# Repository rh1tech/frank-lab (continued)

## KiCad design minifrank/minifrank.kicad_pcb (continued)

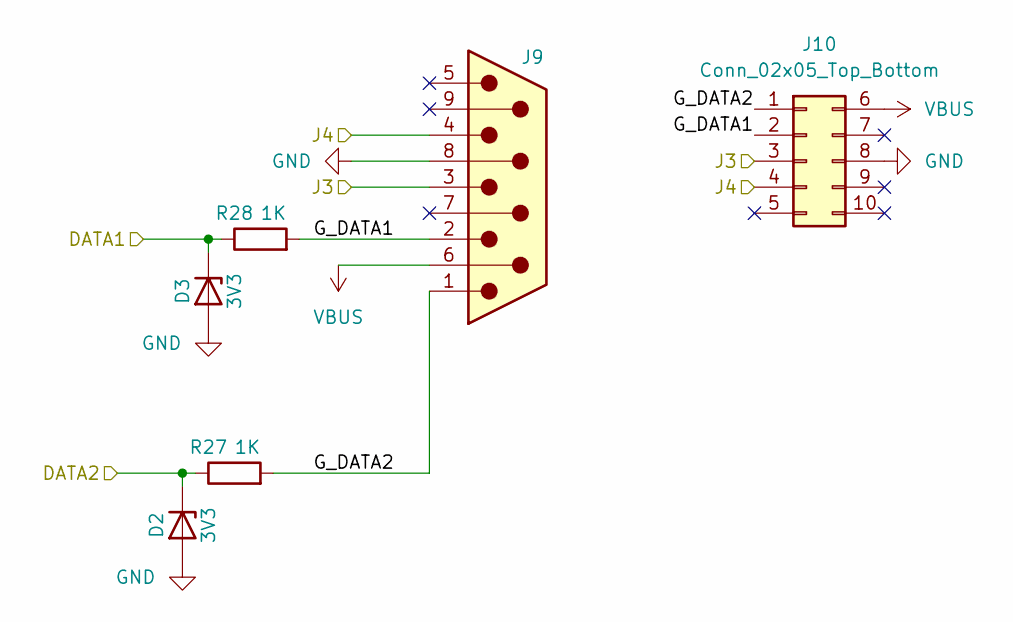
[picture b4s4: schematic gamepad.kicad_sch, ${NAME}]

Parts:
D2, D3: 3V3; Diode (SOD-323)
J9: GP2; DSUB-9_Male_TopMount
J10: Conn_02x05_Top_Bottom; IDC-Header_2x05_P2.54mm_Vertical
R27, R28: 1K; R_0603_1608Metric

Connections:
/GPIO20: J9.4, J10.4; also elsewhere on the board
/GPIO21: J9.3, J10.3; also elsewhere on the board
/GPIO26: D3.1 (K), R28.1; also elsewhere on the board
/GPIO27: D2.1 (K), R27.1; also elsewhere on the board
/Gamepad/G_DATA1: J9.2, J10.2, R28.2
/Gamepad/G_DATA2: J9.1, J10.1, R27.2

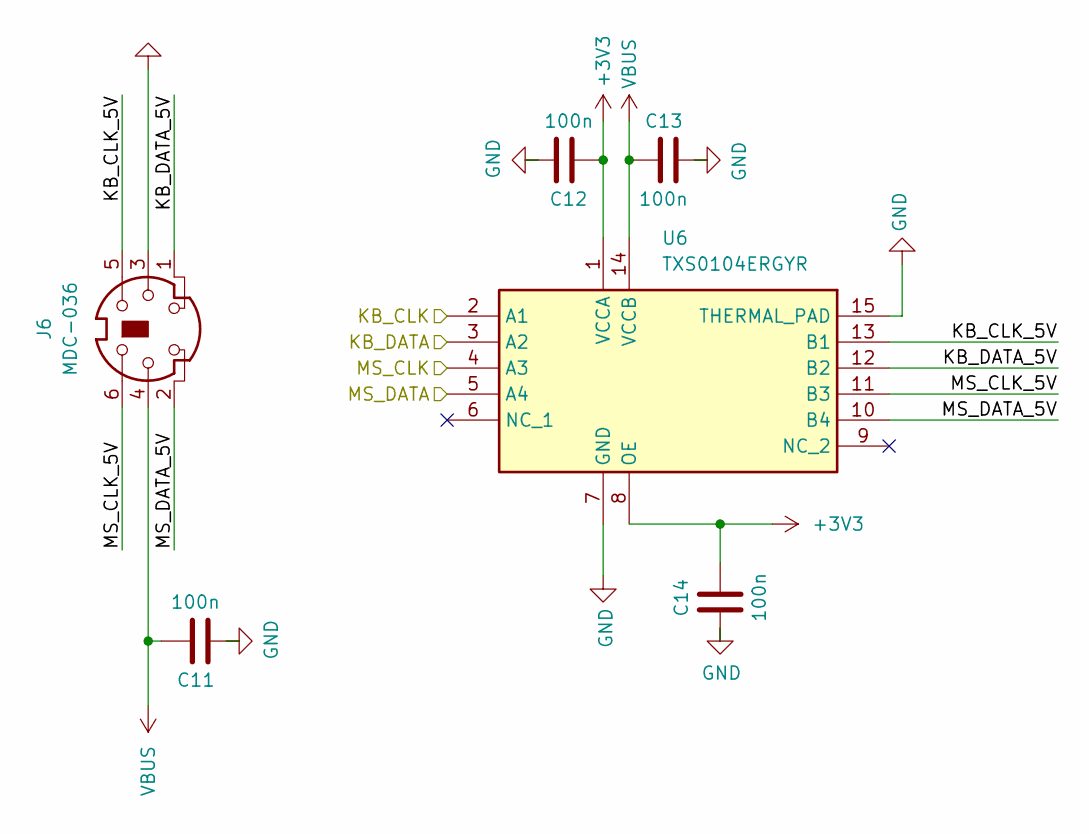
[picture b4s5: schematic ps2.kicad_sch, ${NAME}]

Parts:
C11, C12, C13, C14: 100n; C_0603_1608Metric
J6: MDC-036; MiniDIN (6 Pin, female)
U6: TXS0104ERGYR; RGY_S-PVQFN-N14_; Mouser Part Number 595-TXS0104ERGYR

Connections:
+3V3: C12.1, C14.1, U6.1 (VCCA), U6.8 (OE); also elsewhere on the board
/GPIO0: U6.4 (A3); also elsewhere on the board
/GPIO1: U6.5 (A4); also elsewhere on the board
/GPIO2: U6.2 (A1); also elsewhere on the board
/GPIO3: U6.3 (A2); also elsewhere on the board
/PS2/KB_CLK_5V: J6.5, U6.13 (B1)
/PS2/KB_DATA_5V: J6.1, U6.12 (B2)
/PS2/MS_CLK_5V: J6.6, U6.11 (B3)
/PS2/MS_DATA_5V: J6.2, U6.10 (B4)

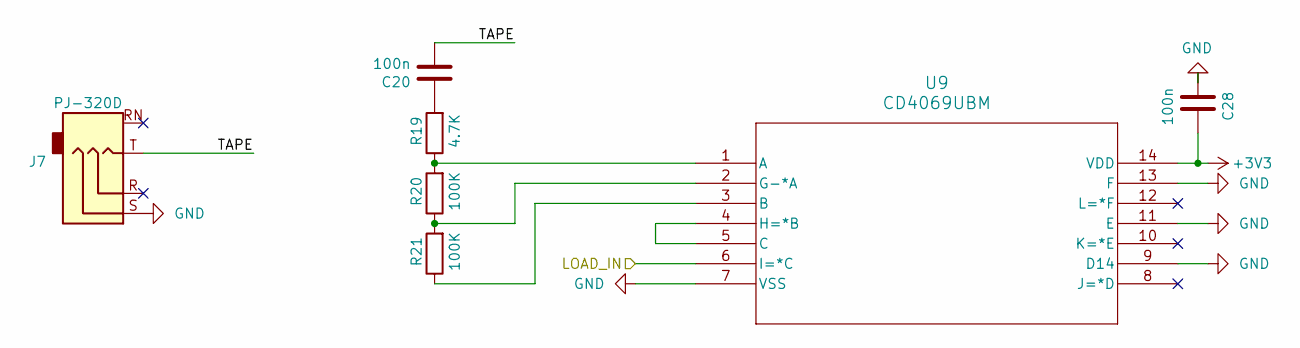
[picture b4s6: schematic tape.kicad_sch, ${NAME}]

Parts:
C20, C28: 100n; C_0603_1608Metric
J7: PJ-320D; Jack (3.5mm, PJ-320D, TapeIn)
R19: 4.7K; R_0603_1608Metric
R20, R21: 100K; R_0603_1608Metric
U9: CD4069UBM; SOIC127P600X175-14N

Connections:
+3V3: C28.1, U9.14 (VDD); also elsewhere on the board
/Tape In/LOAD_IN: U9.6 (I=*C); also elsewhere on the board
/Tape In/TAPE: C20.2, J7.T
unnamed: C20.1, R19.2
unnamed: R19.1, R20.2, U9.1 (A)
unnamed: R21.1, U9.3 (B)
unnamed: U9.4 (H=*B), U9.5 (C)
unnamed: R20.1, R21.2, U9.2 (G-*A)

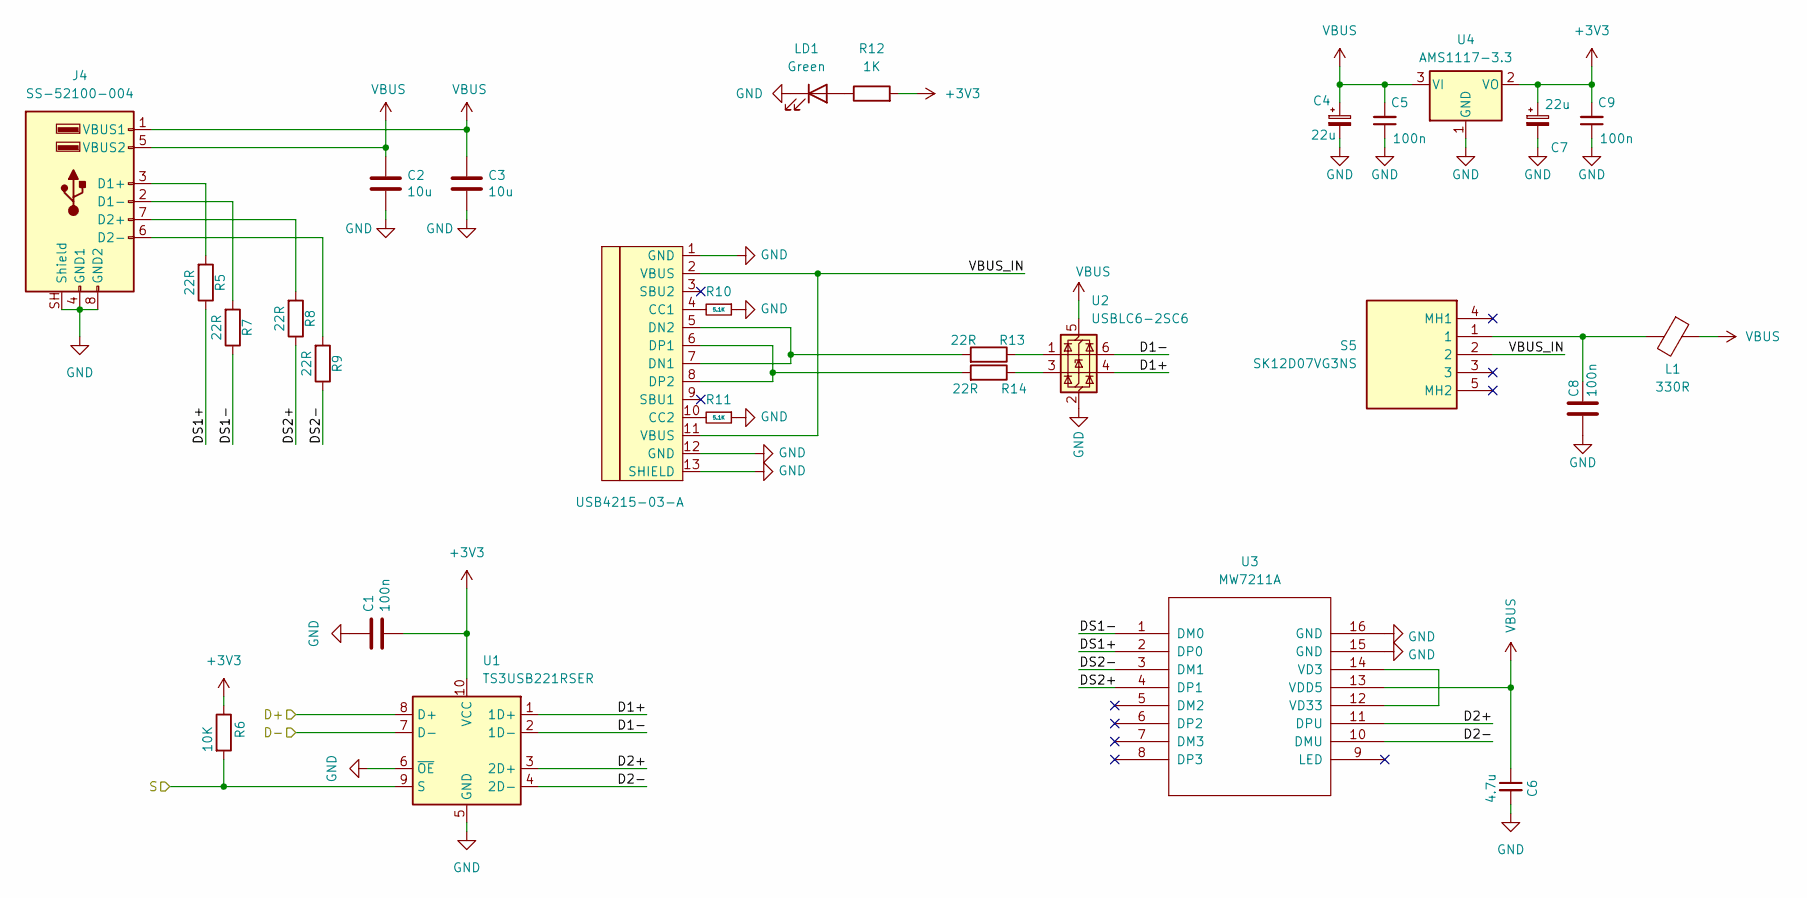
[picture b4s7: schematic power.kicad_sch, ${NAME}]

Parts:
C1, C5, C8, C9: 100n; C_0603_1608Metric
C2, C3: 10u; C_0603_1608Metric
C4, C7: 22u; Capacitor (3528, tantalum, polar)
C6: 4.7u; C_0603_1608Metric; LCSC C1746
J4: SS-52100-004; USB Type A (stacked)
J5: USB4215-03-A; USB Type C; LCSC C165948
L1: 330R; L_0603_1608Metric
LD1: Green; LED_0603_1608Metric
R5, R7, R8, R9, R13, R14: 22R; R_0603_1608Metric
R6: 10K; R_0603_1608Metric
R10, R11: 5.1K; R_0603_1608Metric
R12: 1K; R_0603_1608Metric
S5: SK12D07VG3NS; Mouser Part Number 611-SK12D07VG3NS
U1: TS3USB221RSER; UQFN-10
U2: USBLC6-2SC6; SOT-23-6
U3: MW7211A; SOP-16
U4: AMS1117-3.3; SOT-89-3

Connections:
+3V3: C1.2, C7.1, C9.2, R6.1, R12.2, U1.10 (VCC), U4.2 (VO); also elsewhere on the board
/D+: U1.8 (D+); also elsewhere on the board
/D-: U1.7 (D-); also elsewhere on the board
/Power/D1+: U1.1 (1D+), U2.4 (I/O2)
/Power/D1-: U1.2 (1D-), U2.6 (I/O1)
/Power/D2+: U1.3 (2D+), U3.11 (DPU)
/Power/D2-: U1.4 (2D-), U3.10 (DMU)
/Power/DS1+: R5.1, U3.2 (DP0)
/Power/DS1-: R7.1, U3.1 (DM0)
/Power/DS2+: R8.1, U3.4 (DP1)
/Power/DS2-: R9.1, U3.3 (DM1)
/Power/VBUS_IN: J5.2 (VBUS), J5.11 (VBUS), S5.2
/USBSW: R6.2, U1.9 (S); also elsewhere on the board
unnamed: C8.1, L1.2, S5.1
unnamed: J4.3 (D1+), R5.2
unnamed: J4.2 (D1-), R7.2
unnamed: J4.7 (D2+), R8.2
unnamed: J4.6 (D2-), R9.2
unnamed: J5.4 (CC1), R10.2
unnamed: J5.10 (CC2), R11.2
unnamed: J5.5 (DN2), J5.7 (DN1), R13.2
unnamed: J5.6 (DP1), J5.8 (DP2), R14.2
unnamed: LD1.2 (A), R12.1
unnamed: R13.1, U2.1 (I/O1)
unnamed: R14.1, U2.3 (I/O2)
unnamed: U3.12 (VD33), U3.14 (VD3)

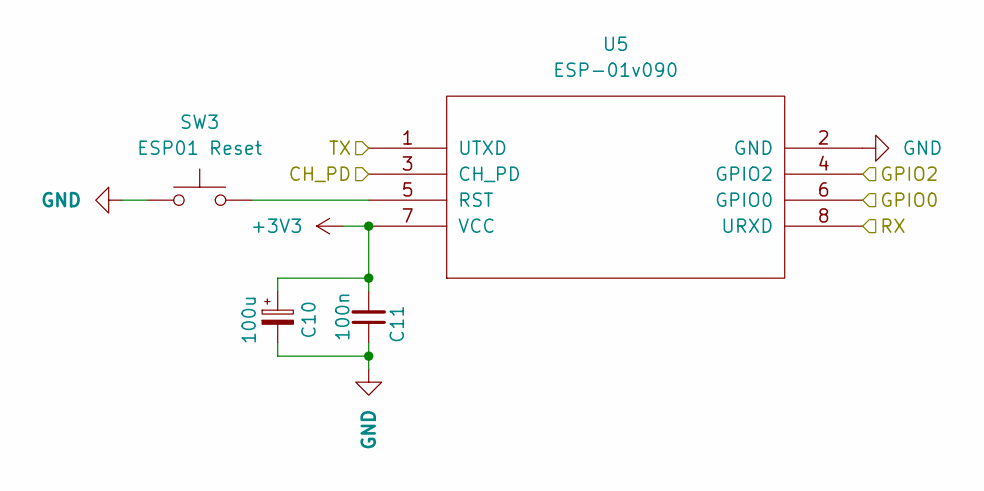
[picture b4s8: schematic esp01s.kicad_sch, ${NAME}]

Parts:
C10: 100u; C_Radial_D6.3mm_P2.50mm
C11: 100n; Combined_0805_CR
SW3: ESP01 Reset; SW_PUSH_6mm_H5mm
U5: ESP-01v090; ESP-01S

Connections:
/Audio Multiplexer/AMP_IN_L: U5.13 (1Z); also elsewhere on the board
/Audio Multiplexer/AMP_IN_R: U5.3 (2Z); also elsewhere on the board
/Audio Multiplexer/AUDIOSW: U5.10 (S0); also elsewhere on the board
/Audio Multiplexer/TDA_L: U5.14 (1Y1); also elsewhere on the board
/Audio Multiplexer/TDA_R: SW3.1, U5.5 (2Y1); also elsewhere on the board
/Audio Multiplexer/TS_OUT_L: U5.12 (1Y0); also elsewhere on the board
/Audio Multiplexer/TS_OUT_R: U5.1 (2Y0); also elsewhere on the board

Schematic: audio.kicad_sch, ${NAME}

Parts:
J12: PJ-320D; Jack (3.5mm, PJ-320D, AudioOut)
J13: Ext_Sound; IDC-Header_2x05_P2.54mm_Vertical

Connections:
+3V3: J13.10; also elsewhere on the board
/Audio Multiplexer/TS_OUT_L: J13.3; also elsewhere on the board
/Audio Multiplexer/TS_OUT_R: J13.5; also elsewhere on the board
/Audio/AMP_OUTL: J12.T; also elsewhere on the board
/Audio/AMP_OUTR: J12.R; also elsewhere on the board
/GPIO9: J13.4; also elsewhere on the board
/GPIO10: J13.1; also elsewhere on the board
/GPIO11: J13.2; also elsewhere on the board

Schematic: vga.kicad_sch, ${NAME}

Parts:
J11: VGA; D-SUB (15 pin, female)
R29, R30, R31: 330R; R_0603_1608Metric
R32, R33, R34: 1K; R_0603_1608Metric
R35, R36: 100R; R_0603_1608Metric

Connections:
/GPIO12: R34.1; also elsewhere on the board
/GPIO13: R31.1; also elsewhere on the board
/GPIO14: R33.1; also elsewhere on the board
/GPIO15: R30.1; also elsewhere on the board
/GPIO16: R32.1; also elsewhere on the board
/GPIO17: R29.1; also elsewhere on the board
/GPIO18: R35.2; also elsewhere on the board
/GPIO19: R36.2; also elsewhere on the board
unnamed: J11.1, R29.2, R32.2
unnamed: J11.2, R30.2, R33.2
unnamed: J11.3, R31.2, R34.2
unnamed: J11.13, R35.1
unnamed: J11.14, R36.1

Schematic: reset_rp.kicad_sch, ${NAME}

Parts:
S1: RP Reset; KMR_2; Mouser Part Number 611-KMR221G-LFS

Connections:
/USBSW: S1.1, S1.3; also elsewhere on the board

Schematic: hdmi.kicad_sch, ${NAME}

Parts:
C25: 100n; C_0603_1608Metric
D1: 1N5819WS; Diode (SOD-323)
J8: DC3RX19JA2; HDMI (female)
RN1, RN2: 270R; Resistor Array (4x0603)

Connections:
/GPIO12: RN1.4 (R4.1); also elsewhere on the board
/GPIO13: RN1.3 (R3.1); also elsewhere on the board
/GPIO14: RN1.2 (R2.1); also elsewhere on the board
/GPIO15: RN1.1 (R1.1); also elsewhere on the board
/GPIO16: RN2.4 (R4.1); also elsewhere on the board
/GPIO17: RN2.3 (R3.1); also elsewhere on the board
/GPIO18: RN2.2 (R2.1); also elsewhere on the board
/GPIO19: RN2.1 (R1.1); also elsewhere on the board
unnamed: C25.1, D1.1 (K), J8.18 (+5V)
unnamed: J8.12 (CLKN), RN1.5 (R4.2)
unnamed: J8.10 (CLKP), RN1.6 (R3.2)
unnamed: J8.9 (D0N), RN1.7 (R2.2)
unnamed: J8.7 (D0P), RN1.8 (R1.2)
unnamed: J8.6 (D1N), RN2.5 (R4.2)
unnamed: J8.4 (D1P), RN2.6 (R3.2)
unnamed: J8.3 (D2N), RN2.7 (R2.2)
unnamed: J8.1 (D2P), RN2.8 (R1.2)

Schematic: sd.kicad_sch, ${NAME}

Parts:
C44: 100n; C_0603_1608Metric
J14: 104031-0811; MicroSD (SMD, long)

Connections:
+3V3: C44.2, J14.4 (VDD); also elsewhere on the board
/GPIO4: J14.7 (DAT0); also elsewhere on the board
/GPIO5: J14.2 (DAT3/CD); also elsewhere on the board
/GPIO6: J14.5 (CLK); also elsewhere on the board
/GPIO7: J14.3 (CMD); also elsewhere on the board

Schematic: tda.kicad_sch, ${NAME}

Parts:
C34, C36: 10u; C_0603_1608Metric
C35: 100n; C_0603_1608Metric
R37: 100R; R_0603_1608Metric
R38, R39: 470R; R_0603_1608Metric
U12: TDA1387T; SO-8

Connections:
/Audio Multiplexer/TDA_L: R39.2, U12.6 (A_LEFT); also elsewhere on the board
/Audio Multiplexer/TDA_R: R38.1, U12.8 (A_RIGHT); also elsewhere on the board
/GPIO9: U12.3 (DATA); also elsewhere on the board
/GPIO10: U12.1 (SCLK); also elsewhere on the board
/GPIO11: U12.2 (LRCK); also elsewhere on the board
unnamed: C36.1, U12.7 (FLT)
unnamed: C34.1, C35.1, R37.1, U12.5 (VA)

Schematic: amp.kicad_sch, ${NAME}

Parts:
C37, C38, C39, C41, C42: 10u; C_0603_1608Metric
C40: 10u; Capacitor (3528, tantalum, polar)
C43: 100n; C_0603_1608Metric
R40, R41, R42, R43, R44, R45: 10K; R_0603_1608Metric
R46, R47: 47K; R_0603_1608Metric
R48, R49: 20K; R_0603_1608Metric
R50: 100R; R_0603_1608Metric
U13: LM358; SO-8

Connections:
/Audio Multiplexer/AMP_IN_L: C37.1, R40.1; also elsewhere on the board
/Audio Multiplexer/AMP_IN_R: C38.1, R41.1; also elsewhere on the board
/Audio/AMP_OUTL: C41.2, R48.2; also elsewhere on the board
/Audio/AMP_OUTR: C42.2, R49.2; also elsewhere on the board
unnamed: C37.2, R44.2
unnamed: C38.2, R45.2
unnamed: C41.1, R46.1, U13.7
unnamed: C42.1, R47.1, U13.1
unnamed: C39.2, R42.1, R43.2, U13.3 (+), U13.5 (+)
unnamed: R45.1, R47.2, U13.2 (-)
unnamed: R44.1, R46.2, U13.6 (-)
unnamed: C40.1, C43.2, R42.2, R50.2, U13.8 (V+)

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
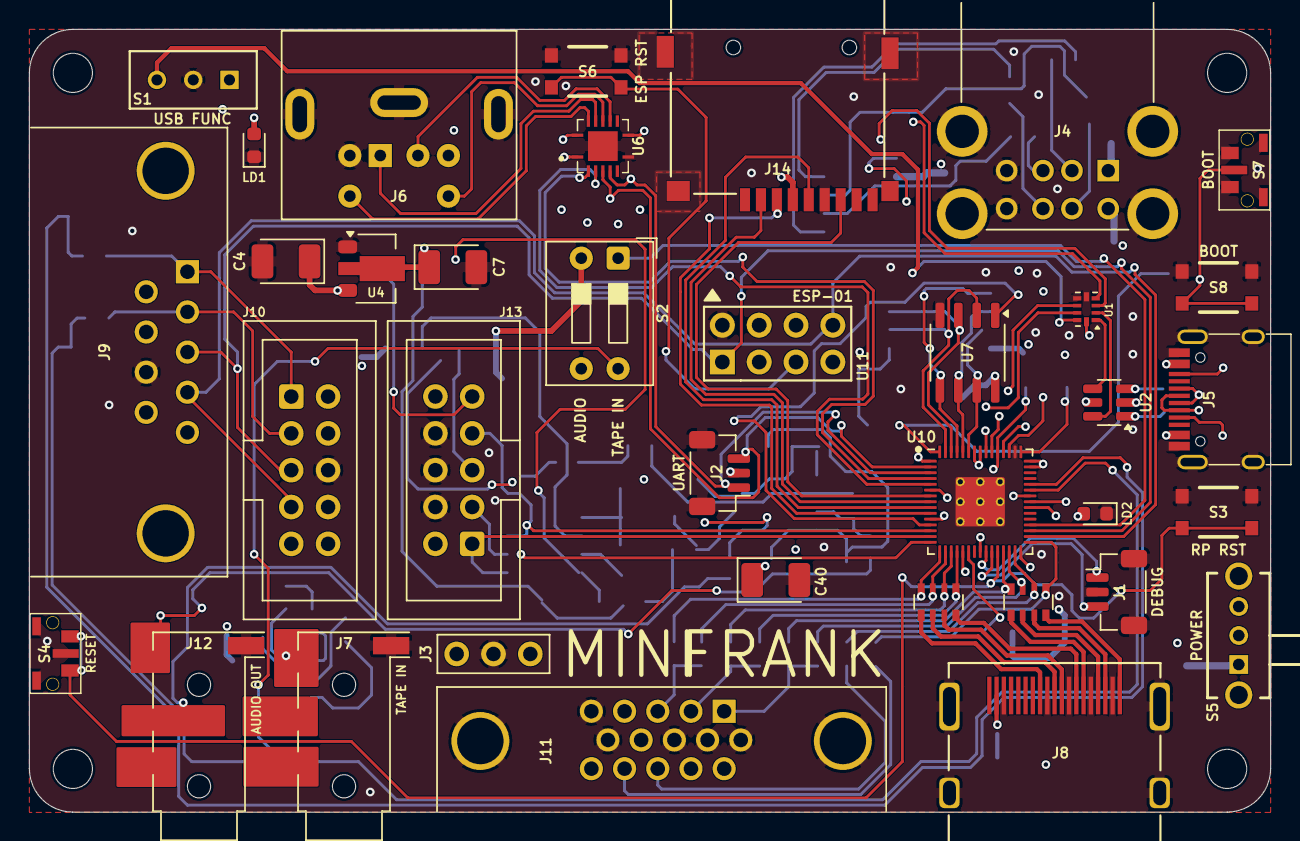
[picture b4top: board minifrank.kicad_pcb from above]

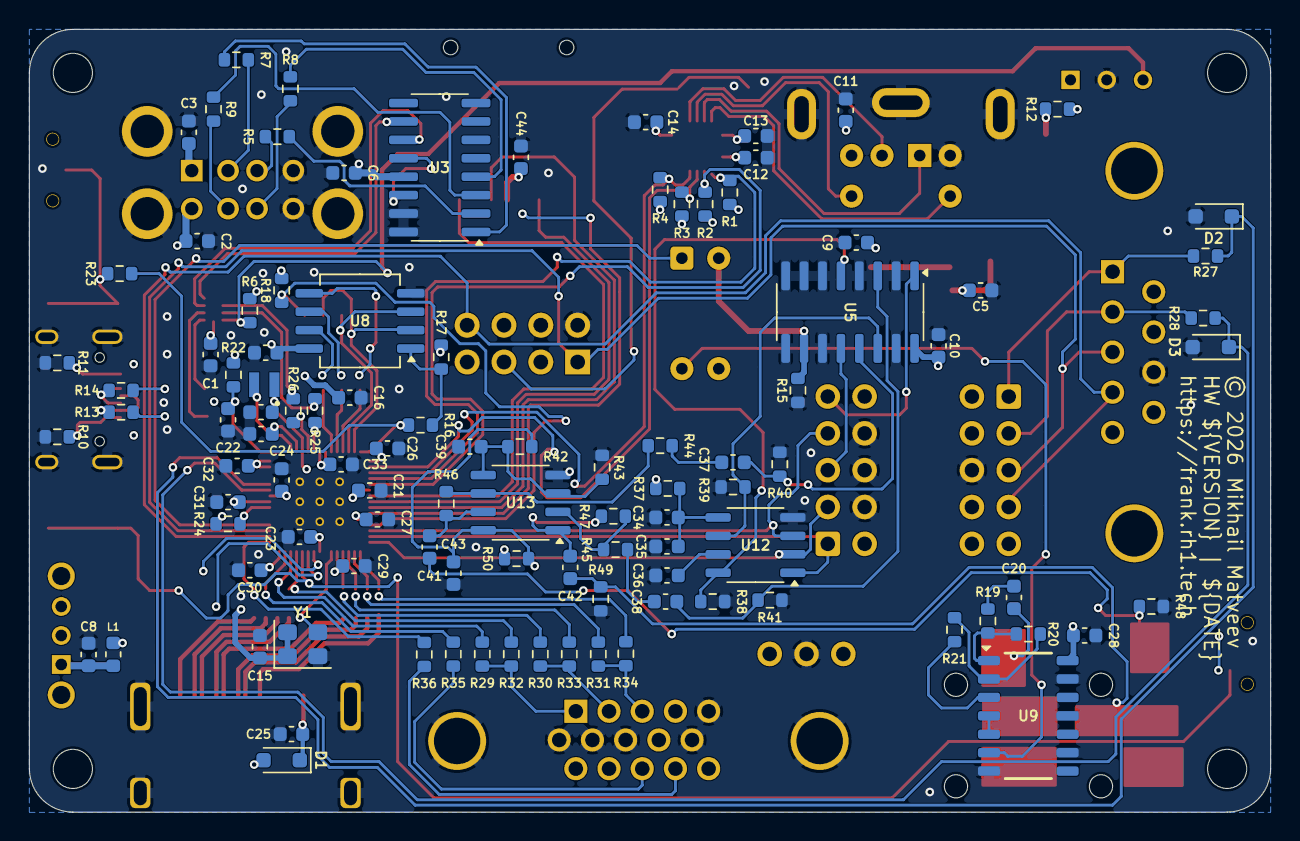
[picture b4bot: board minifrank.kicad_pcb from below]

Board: 4 copper layers, 85.6 x 54.0 mm, 143 parts (103 on the bottom side), 119 nets.

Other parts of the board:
R15: 10K; R_0603_1608Metric
S3: RP Reset; KMR_2
S4: RP Reset; TS-1234VW
S6: ESP Reset; KMR_2
U11: ESP-01v090; ESP-01

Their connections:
+3V3: U11.7 (VCC); also elsewhere on the board
/Audio Multiplexer/AUDIOSW: R15.2; also elsewhere on the board
/ESP_RST: S6.2, S6.4, U11.5 (RST)
/GPIO20: U11.8 (URXD); also elsewhere on the board
/GPIO21: U11.1 (UTXD); also elsewhere on the board
/RUN: S3.2, S3.4, S4.1; also elsewhere on the board

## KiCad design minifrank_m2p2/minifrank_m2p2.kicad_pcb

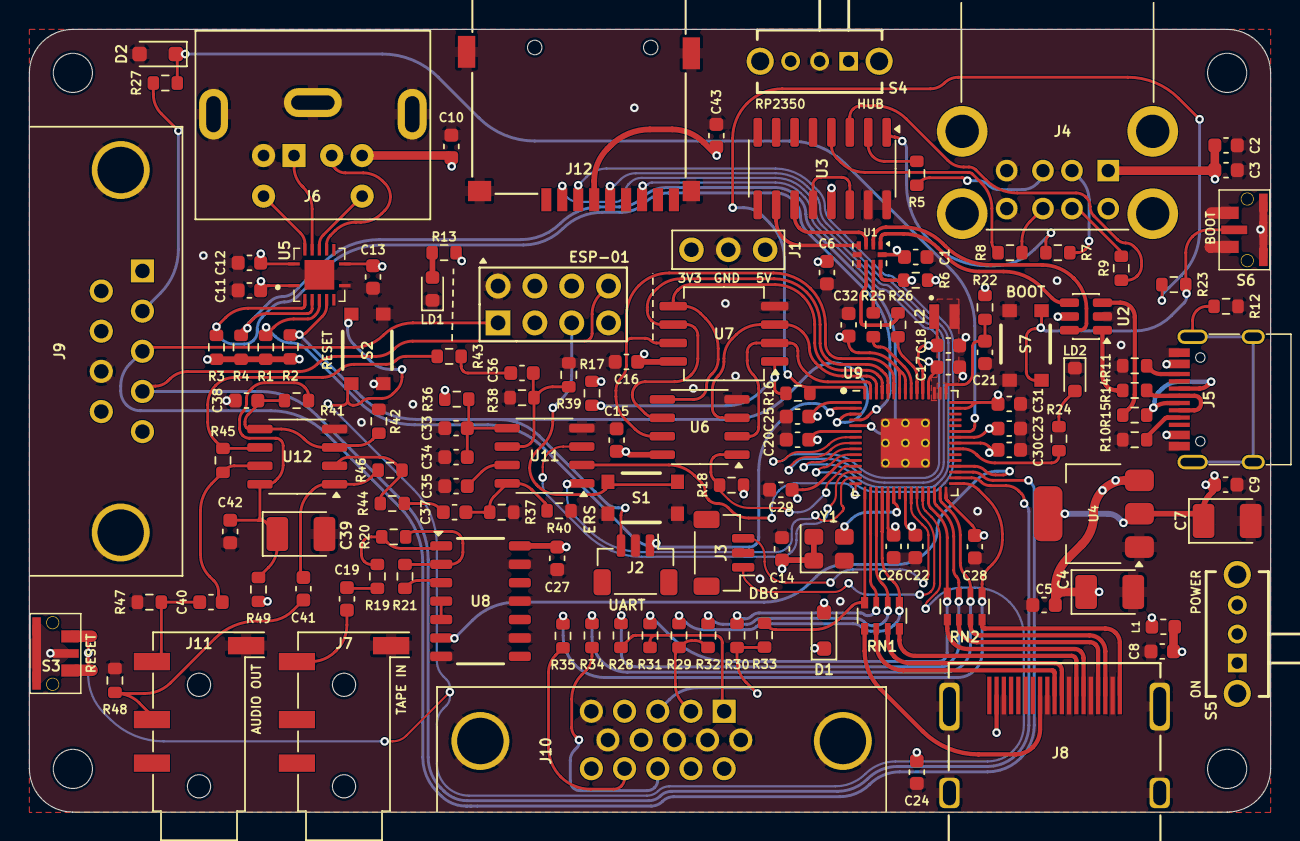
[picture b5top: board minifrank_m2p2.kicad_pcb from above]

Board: 4 copper layers, 85.6 x 54.0 mm, 136 parts (0 on the bottom side), 112 nets.

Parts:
C1, C5, C8, C9, C10, C11, C12, C13, C14, C15, C16, C19, C20, C23, C24, C25, C26, C27, C28, C29, C30, C31, C32, C34, C42, C43: 100n; C_0603_1608Metric
C2, C3, C33, C35, C36, C37, C38, C40, C41: 10u; C_0603_1608Metric
C4, C7: 22u; Capacitor (3528, tantalum, polar)
C6, C17, C18, C21, C22: 4.7u; C_0603_1608Metric
C39: 10u; Capacitor (3528, tantalum, polar)
D1: 1N5819WS; Diode (SOD-323)
D2: 3V3; Diode (SOD-323)
H1, H2, H3, H4: Hole 2.7mm; Mounting Hole (2.7mm)
J1: PWR; Pin Header (1x03)
J2: UART; JST_SH_BM03B-SRSS-TB_1x03-1MP_P1.00mm_Vertical
J3: DEBUG; JST_SH_BM03B-SRSS-TB_1x03-1MP_P1.00mm_Vertical
J4: SS-52100-004; USB Type A (stacked)
J5: USB4215-03-A; USB Type C
J6: MDC-036; MiniDIN (6 Pin, female)
J7, J11: PJ-320D; Jack (3.5mm, PJ-320D)
J8: DC3RX19JA2; HDMI (female)
J9: GP2; D-SUB (9 pin, male, top mount)
J10: VGA; D-SUB (15 pin, female)
J12: 104031-0811; MicroSD (SMD, long)
L1: 330R; L_0603_1608Metric
L2: 3.3u; L_pol_2016
LD1: Green; LED_0603_1608Metric
LD2: Blue; LED_0603_1608Metric
R1, R2, R3, R4, R6, R17, R18, R39, R40, R41, R42, R43, R44: 10K; R_0603_1608Metric
R5, R7, R8, R9, R14, R15: 22R; R_0603_1608Metric
R10, R11: 5.1K; R_0603_1608Metric
R12: 1M; R_0603_1608Metric
R13, R23, R24, R27, R31, R32, R33: 1K; R_0603_1608Metric
R16: 0R; R_0603_1608Metric
R19: 4.7K; R_0603_1608Metric
R20, R21: 100K; R_0603_1608Metric
R22: 33R; R_0603_1608Metric
R25, R26: 27R; R_0603_1608Metric
R28, R29, R30: 330R; R_0603_1608Metric
R34, R35, R36, R49: 100R; R_0603_1608Metric
R37, R38: 470R; R_0603_1608Metric
R45, R46: 47K; R_0603_1608Metric
R47, R48: 20K; R_0603_1608Metric
RN1, RN2: 270R; Resistor Array (4x0603)
S1: ESP Reset; KMR_2
S2, S7: RP Reset; KMR_2
S3, S6: RP Reset; TS-1234VW
S4, S5: SK12D07VG3NS
U1: TS3USB221RSER; UQFN-10
U2: USBLC6-2SC6; SOT-23-6
U3: MW7211A; SOP-16
U4: NCP1117-3.3_SOT223; SOT-223-3_TabPin2
U5: TXS0104ERGYR; RGY_S-PVQFN-N14_
U6: ESP-PSRAM32; SO-8
U7: W25Q128JVS; SOIC-8
U8: CD4069UBM; SOIC127P600X175-14N
U9: RP2350; QFN 60 (RP2350A)
U10: ESP-01v090; ESP-01
U11: TDA1387T; SO-8
U12: LM358; SO-8
Y1: ASE-12MHz; Oscillator_SMD_Abracon_ASE-4Pin_3.2x2.5mm

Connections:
+1V1: C18.1, C20.1, C22.1, C23.1, L2.1, U9.6 (DVDD), U9.23 (DVDD), U9.39 (DVDD), U9.50 (VREG_FB)
+3V3: C1.2, C7.1, C9.2, C11.1, C13.1, C14.1, C15.1, C16.1, C17.1, C25.1, C26.1, C27.1, C28.1, C29.1, C30.1, C31.1, C32.1, C43.2, J1.1, J12.4 (VDD), R1.2, R2.2, R3.2, R4.2, R6.1, R13.2, R17.1, R18.2, R22.1, U1.10 (VCC), U4.2 (VO), U5.1 (VCCA), U5.8 (OE), U6.8 (VCC), U7.8 (VCC), U8.14 (VDD), U9.1 (IOVDD), U9.11 (IOVDD), U9.20 (IOVDD), U9.30 (IOVDD), U9.38 (IOVDD), U9.44 (ADC_AVDD), U9.45 (IOVDD), U9.49 (VREG_VIN), U9.53 (USB_OTP_VDD), U9.54 (QSPI_IOVDD), U10.7 (VCC), Y1.1 (EN), Y1.4 (Vdd)
/Audio/AMP_OUTL: C40.2, J11.T, R47.2
/Audio/AMP_OUTR: C41.2, J11.R, R48.2
/Audio/TDA_L: C36.1, R38.2, R39.1, U11.6 (A_LEFT)
/Audio/TDA_R: C37.1, R37.1, R40.1, U11.8 (A_RIGHT)
/D+: R25.1, U1.8 (D+)
/D-: R26.1, U1.7 (D-)
/ESP_RST: S1.2, S1.4, U10.5 (RST)
/GPIO0: J2.1, R1.1, U5.4 (A3), U9.2 (GPIO0)
/GPIO1: J2.3, R2.1, U5.5 (A4), U9.3 (GPIO1)
/GPIO2: R3.1, U5.2 (A1), U9.4 (GPIO2)
/GPIO3: R4.1, U5.3 (A2), U9.5 (GPIO3)
/GPIO4: J12.7 (DAT0), U9.7 (GPIO4)
/GPIO5: J12.2 (DAT3/CD), U9.8 (GPIO5)
/GPIO6: J12.5 (CLK), U9.9 (GPIO6)
/GPIO7: J12.3 (CMD), U9.10 (GPIO7)
/GPIO9: U9.13 (GPIO9), U11.3 (DATA)
/GPIO10: U9.14 (GPIO10), U11.1 (SCLK)
/GPIO11: U9.15 (GPIO11), U11.2 (LRCK)
/GPIO12: R33.1, RN1.4 (R4.1), U9.16 (GPIO12)
/GPIO13: R30.1, RN1.3 (R3.1), U9.17 (GPIO13)
/GPIO14: R32.1, RN1.2 (R2.1), U9.18 (GPIO14)
/GPIO15: R29.1, RN1.1 (R1.1), U9.19 (GPIO15)
/GPIO16: R31.1, RN2.4 (R4.1), U9.27 (GPIO16)
/GPIO17: R28.1, RN2.3 (R3.1), U9.28 (GPIO17)
/GPIO18: R34.2, RN2.2 (R2.1), U9.29 (GPIO18)
/GPIO19: R35.2, RN2.1 (R1.1), U9.31 (GPIO19)
/GPIO20: J9.4, U9.32 (GPIO20), U10.8 (URXD)
/GPIO21: J9.3, U9.33 (GPIO21), U10.1 (UTXD)
/GPIO22: U8.6 (I=*C), U9.34 (GPIO22)
/GPIO26: D2.1 (K), R27.1, U9.40 (GPIO26_ADC0)
/PS2/KB_CLK_5V: J6.5, U5.13 (B1)
/PS2/KB_DATA_5V: J6.1, U5.12 (B2)
/PS2/MS_CLK_5V: J6.6, U5.11 (B3)
/PS2/MS_DATA_5V: J6.2, U5.10 (B4)
/Power/D1+: U1.1 (1D+), U2.4 (I/O2)
/Power/D1-: U1.2 (1D-), U2.6 (I/O1)
/Power/D2+: U1.3 (2D+), U3.11 (DPU)
/Power/D2-: U1.4 (2D-), U3.10 (DMU)
/Power/DS1+: R5.1, U3.2 (DP0)
/Power/DS1-: R7.1, U3.1 (DM0)
/Power/DS2+: R8.1, U3.4 (DP1)
/Power/DS2-: R9.1, U3.3 (DM1)
/Power/VBUS_IN: J5.2 (VBUS), J5.11 (VBUS), S5.2
/RP2350A/FLASH_SS: R16.2, R17.2, U7.1 (~CS)
/RP2350A/GPIO8: R18.1, U6.1 (~CE), U9.12 (GPIO8)
/RP2350A/QSPI_SCLK: U6.6 (SCLK), U7.6 (CLK), U9.56 (QSPI_SCLK)
/RP2350A/QSPI_SD0: U6.5 (SI/SIO), U7.5 (DI(IO0)), U9.57 (QSPI_SD0)
/RP2350A/QSPI_SD1: U6.2 (SO/SIO), U7.2 (DO(IO1)), U9.59 (QSPI_SD1)
/RP2350A/QSPI_SD2: U6.3 (SIO2), U7.3 (IO2), U9.58 (QSPI_SD2)
/RP2350A/QSPI_SD3: U6.7 (SIO3), U7.7 (IO3), U9.55 (QSPI_SD3)
/RP2350A/QSPI_SS: R16.1, R23.1, U9.60 (QSPI_SS)
/RP2350A/SWCLK: J3.3, U9.24 (SWCLK)
/RP2350A/SWD: J3.1, U9.25 (SWD)
/RP2350A/VREG_AVDD: C21.1, R22.2, U9.46 (VREG_AVDD)
/RP2350A/VREG_LX: L2.2, U9.48 (VREG_LX)
/RP2350A/XIN: U9.21 (XIN), Y1.3 (OUT)
/RP2350A/~USB_BOOT: R23.2, S6.2, S7.2, S7.4
/RUN: S2.2, S2.4, S3.1, U9.26 (RUN)
/Tape In/TAPE: C19.2, J7.T
/USBSW: R6.2, S4.3, U1.9 (S)
GND: C1.1, C2.2, C3.2, C4.2, C5.1, C6.2, C7.2, C8.2, C9.1, C10.2, C11.2, C12.2, C13.2, C14.2, C15.2, C16.2, C17.2, C18.2, C20.2, C21.2, C22.2, C23.2, C24.2, C25.2, C26.2, C27.2, C28.2, C29.2, C30.2, C31.2, C32.2, C33.2, C34.2, C35.2, C38.1, C39.2, C42.1, C43.1, D2.2 (A), J1.2, J2.2, J3.2, J4.4 (GND1), J4.8 (GND2), J5.1 (GND), J5.12 (GND), J6.3, J7.S, J8.2 (G_D2), J8.5 (G_D1), J8.8 (G_D0), J8.11 (G_CLK), J8.17 (G_DDC/CEC), J8.20 (SHIELD1), J8.21 (SHIELD2), J8.22 (SHIELD3), J8.23 (SHIELD4), J9.8, J10.0, J10.5, J10.6, J10.7, J10.8, J10.10, J11.S, J12.6 (VSS), LD1.1 (K), LD2.1 (K), R10.1, R11.1, R12.2, R37.2, R38.1, R39.2, R40.2, R42.1, R47.1, R48.1, S1.1, S1.3, S2.1, S2.3, S3.2, S3.3 (GND), S4.2, S6.1, S6.3 (GND), S7.1, S7.3, U1.5 (GND), U1.6 (~OE), U2.2 (GND), U3.15 (GND), U3.16 (GND), U4.1 (GND), U5.7 (GND), U5.15 (THERMAL_PAD), U6.4 (VSS), U7.4 (GND), U8.7 (VSS), U8.9 (D14), U8.11 (E), U8.13 (F), U9.47 (VREG_PGND), U9.61 (GND), U10.2 (GND), U11.4 (AGND), U12.4 (V-), Y1.2 (GND)
GPIO25: R24.2, U9.37 (GPIO25)
unnamed: C8.1, L1.2, S5.1
unnamed: C19.1, R19.2
unnamed: C36.2, R43.2
unnamed: C37.2, R44.2
unnamed: C40.1, R45.1, U12.7
unnamed: C41.1, R46.1, U12.1
unnamed: C24.1, D1.1 (K), J8.18 (+5V)
unnamed: J4.3 (D1+), R5.2
unnamed: J4.2 (D1-), R7.2
unnamed: J4.7 (D2+), R8.2
unnamed: J4.6 (D2-), R9.2
unnamed: J5.4 (CC1), R10.2
unnamed: J5.10 (CC2), R11.2
unnamed: J5.5 (DN2), J5.7 (DN1), R14.2
unnamed: J5.6 (DP1), J5.8 (DP2), R15.2
unnamed: J5.13 (SHIELD), R12.1
unnamed: J8.12 (CLKN), RN1.5 (R4.2)
unnamed: J8.10 (CLKP), RN1.6 (R3.2)
unnamed: J8.9 (D0N), RN1.7 (R2.2)
unnamed: J8.7 (D0P), RN1.8 (R1.2)
unnamed: J8.6 (D1N), RN2.5 (R4.2)
unnamed: J8.4 (D1P), RN2.6 (R3.2)
unnamed: J8.3 (D2N), RN2.7 (R2.2)
unnamed: J8.1 (D2P), RN2.8 (R1.2)
unnamed: J9.2, R27.2
unnamed: J10.1, R28.2, R31.2
unnamed: J10.2, R29.2, R32.2
unnamed: J10.3, R30.2, R33.2
unnamed: J10.13, R34.1
unnamed: J10.14, R35.1
unnamed: LD1.2 (A), R13.1
unnamed: LD2.2 (A), R24.1
unnamed: R14.1, U2.1 (I/O1)
unnamed: R15.1, U2.3 (I/O2)
unnamed: U3.12 (VD33), U3.14 (VD3)
unnamed: R19.1, R20.2, U8.1 (A)
unnamed: R21.1, U8.3 (B)
unnamed: U8.4 (H=*B), U8.5 (C)
unnamed: R20.1, R21.2, U8.2 (G-*A)
unnamed: R26.2, U9.51 (USB_DM)
unnamed: R25.2, U9.52 (USB_DP)
unnamed: C35.1, U11.7 (FLT)
unnamed: C33.1, C34.1, R36.1, U11.5 (VA)
unnamed: C38.2, R41.1, R42.2, U12.3 (+), U12.5 (+)
unnamed: R44.1, R46.2, U12.2 (-)
unnamed: R43.1, R45.2, U12.6 (-)
unnamed: C39.1, C42.2, R41.2, R49.2, U12.8 (V+)
VBUS: C2.1, C3.1, C4.1, C5.2, C6.1, C10.1, C12.1, D1.2 (A), J1.3, J4.1 (VBUS1), J4.5 (VBUS2), J6.4, J9.6, L1.1, R36.2, R49.1, U2.5 (VBUS), U3.13 (VDD5), U4.3 (VI), U5.14 (VCCB)

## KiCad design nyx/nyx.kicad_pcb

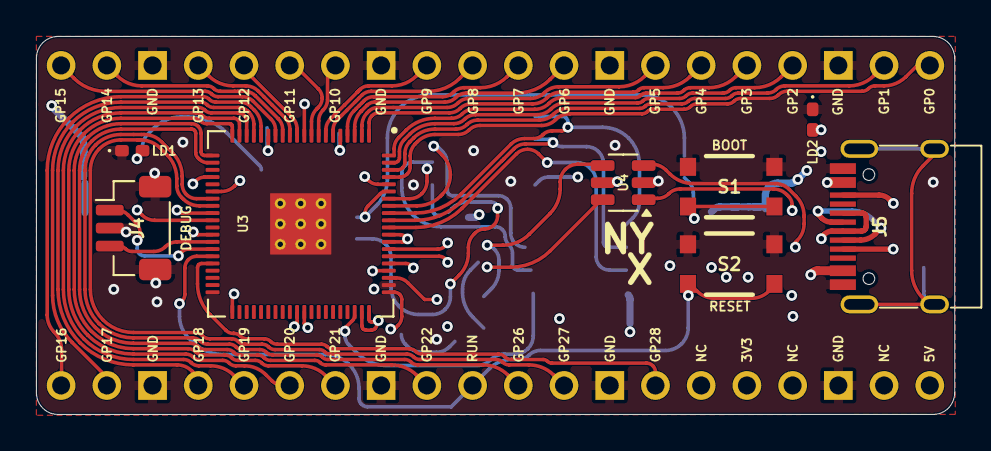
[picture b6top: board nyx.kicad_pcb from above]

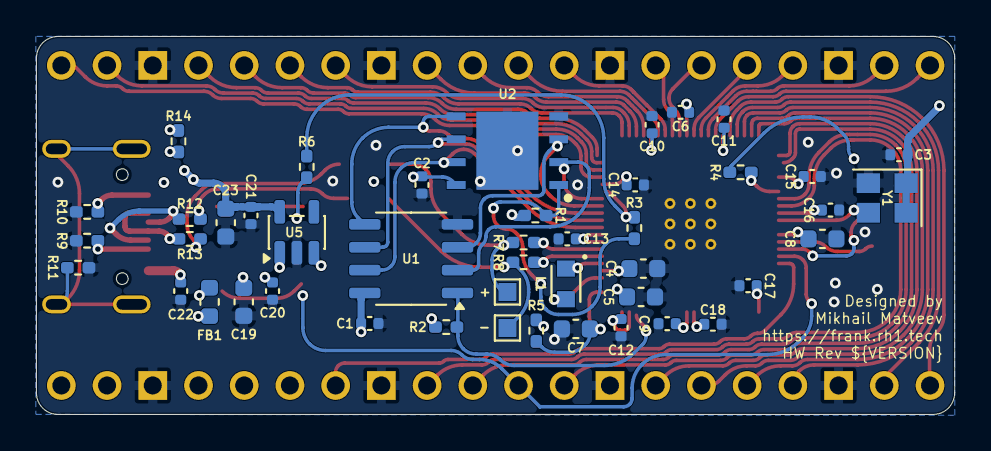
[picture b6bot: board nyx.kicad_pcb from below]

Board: 4 copper layers, 51.0 x 21.0 mm, 54 parts (44 on the bottom side), 61 nets.

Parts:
C1, C2, C3, C6, C9, C10, C11, C12, C13, C14, C15, C16, C17, C18, C20, C21, C22: 100n; C_0402_1005Metric
C4, C5, C7, C8: 4.7u; C_0603_1608Metric
C19, C23: 10u; C_0603_1608Metric
FB1: 330R; L_0603_1608Metric
J1: CON_PICO_21-40
J2: TestPoint_Pad_1.0x1.0mm_x2
J3: CON_PICO_1-20
J4: DEBUG; JST_SH_1x03_P1.00mm_Vertical
J5: USB4215-03-A; USB_C_Receptacle
L1: 3.3u; L_LQH2MCN100K02L
LD1: Blue; LED_0402_1005Metric
LD2: Green; LED_0402_1005Metric
R1, R2: 10K; R_0402_1005Metric
R3: 0R; R_0402_1005Metric
R4, R6, R14: 1K; R_0402_1005Metric
R5: 33; R_0402_1005Metric
R7, R8: 27R; R_0402_1005Metric
R9, R10: 5.1K; R_0402_1005Metric
R11: 1M; R_0402_1005Metric
R12, R13: 22R; R_0402_1005Metric
S1: Boot; Button_SMD_3x4x2mm
S2: RP Reset; Button_SMD_3x4x2mm
U1: ESP-PSRAM32; SO-8_3.9x4.9mm_P1.27mm
U2: W25Q128JVPIQ; SON127P600X500X80-9N-D
U3: RP2350_80QFN; RP2350-QFN-80_10x10_P0.4mm
U4: USBLC6-2SC6; SOT-23-6
U5: ME6211C33M5; SOT-23-5
Y1: ASE-12MHz; Oscillator_SMD_3225_4Pin

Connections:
+1V1: C5.1, C6.1, C8.1, C9.1, L1.1, U3.10 (DVDD), U3.32 (DVDD), U3.51 (DVDD), U3.65 (VREG_FB)
+3V3: C1.1, C2.1, C3.1, C4.1, C10.1, C11.1, C12.1, C13.1, C14.1, C15.1, C16.1, C17.1, C18.1, C21.1, C23.1, J1.36, R1.2, R2.2, R5.1, R14.2, U1.8 (VCC), U2.8 (VCC), U3.5 (IOVDD), U3.15 (IOVDD), U3.24 (IOVDD), U3.29 (IOVDD), U3.41 (IOVDD), U3.50 (IOVDD), U3.59 (ADC_AVDD), U3.60 (IOVDD), U3.64 (VREG_VIN), U3.68 (USB_OTP_VDD), U3.69 (QSPI_IOVDD), U3.76 (IOVDD), U5.5 (V_{OUT}), Y1.1 (EN), Y1.4 (Vdd)
/D+: J2.1, R7.1, U4.4 (I/O2)
/D-: J2.2, R8.1, U4.6 (I/O1)
/GPIO0: J3.1, U3.77 (GPIO0)
/GPIO1: J3.2, U3.78 (GPIO1)
/GPIO2: J3.4, U3.79 (GPIO2)
/GPIO3: J3.5, U3.80 (GPIO3)
/GPIO4: J3.6, U3.1 (GPIO4)
/GPIO5: J3.7, U3.2 (GPIO5)
/GPIO6: J3.9, U3.3 (GPIO6)
/GPIO7: J3.10, U3.4 (GPIO7)
/GPIO8: J3.11, U3.6 (GPIO8)
/GPIO9: J3.12, U3.7 (GPIO9)
/GPIO10: J3.14, U3.8 (GPIO10)
/GPIO11: J3.15, U3.9 (GPIO11)
/GPIO12: J3.16, U3.11 (GPIO12)
/GPIO13: J3.17, U3.12 (GPIO13)
/GPIO14: J3.19, U3.13 (GPIO14)
/GPIO15: J3.20, U3.14 (GPIO15)
/GPIO16: J1.21, U3.16 (GPIO16)
/GPIO17: J1.22, U3.17 (GPIO17)
/GPIO18: J1.24, U3.18 (GPIO18)
/GPIO19: J1.25, U3.19 (GPIO19)
/GPIO20: J1.26, U3.20 (GPIO20)
/GPIO21: J1.27, U3.21 (GPIO21)
/GPIO22: J1.29, U3.22 (GPIO22)
/GPIO26: J1.31, U3.27 (GPIO26)
/GPIO27: J1.32, U3.28 (GPIO27)
/GPIO28: J1.34, U3.36 (GPIO28)
/Power/VBUS_IN: C22.1, FB1.1, J5.2 (VBUS), J5.11 (VBUS)
/RP2350B/GPIO47: R2.1, U1.1 (~CE), U3.58 (GPIO47_ADC7)
/RP2350B/QSPI_SCLK: U1.6 (SCLK), U2.6 (CLK), U3.71 (QSPI_SCLK)
/RP2350B/QSPI_SD0: U1.5 (SI/SIO), U2.5 (DI_(IO0)), U3.72 (QSPI_SD0)
/RP2350B/QSPI_SD1: U1.2 (SO/SIO), U2.2 (DO_(IO1)), U3.74 (QSPI_SD1)
/RP2350B/QSPI_SD2: U1.3 (SIO2), U2.3 (~WP_(IO2)), U3.73 (QSPI_SD2)
/RP2350B/QSPI_SD3: U1.7 (SIO3), U2.7 (~HOLD_OR_/RESET_(IO3)), U3.70 (QSPI_SD3)
/RP2350B/QSPI_SS: R3.1, R6.1, U3.75 (QSPI_SS)
/RP2350B/SWCLK: J4.3, U3.33 (SWCLK)
/RP2350B/SWD: J4.1, U3.34 (SWD)
/RP2350B/VREG_AVDD: C7.1, R5.2, U3.61 (VREG_AVDD)
/RP2350B/VREG_LX: L1.2, U3.63 (VREG_LX)
/RP2350B/XIN: U3.30 (XIN), Y1.3 (OUT)
/RP2350B/~USB_BOOT: R6.2, S1.1, S1.3
/RUN: J1.30, S2.1, S2.3, U3.35 (RUN)
GND: C1.2, C2.2, C3.2, C4.2, C5.2, C6.2, C7.2, C8.2, C9.2, C10.2, C11.2, C12.2, C13.2, C14.2, C15.2, C16.2, C17.2, C18.2, C19.1, C20.1, C21.2, C22.2, C23.2, J1.23, J1.28, J1.33, J1.38, J3.3, J3.8, J3.13, J3.18, J4.2, J5.1 (GND), J5.12 (GND), LD1.1 (K), LD2.1 (K), R9.1, R10.1, R11.2, S1.2, S1.4, S2.2, S2.4, U1.4 (VSS), U2.4 (GND_1), U2.9 (GND_2), U3.62 (VREG_PGND), U3.81 (GND), U4.2 (GND), U5.2 (V_{SS}), Y1.2 (GND)
unnamed: J5.4 (CC1), R9.2
unnamed: J5.10 (CC2), R10.2
unnamed: J5.5 (DN2), J5.7 (DN1), R12.2
unnamed: J5.6 (DP1), J5.8 (DP2), R13.2
unnamed: J5.13 (SHIELD), R11.1
unnamed: LD1.2 (A), R4.1
unnamed: LD2.2 (A), R14.1
unnamed: R12.1, U4.1 (I/O1)
unnamed: R13.1, U4.3 (I/O2)
unnamed: R1.1, R3.2, U2.1 (~CS)
unnamed: R4.2, U3.26 (GPIO25)
unnamed: R8.2, U3.66 (USB_DM)
unnamed: R7.2, U3.67 (USB_DP)
unnamed: C19.2, C20.2, FB1.2, U5.1 (V_{IN}), U5.3 (CE)
VBUS: J1.40, U4.5 (VBUS)
